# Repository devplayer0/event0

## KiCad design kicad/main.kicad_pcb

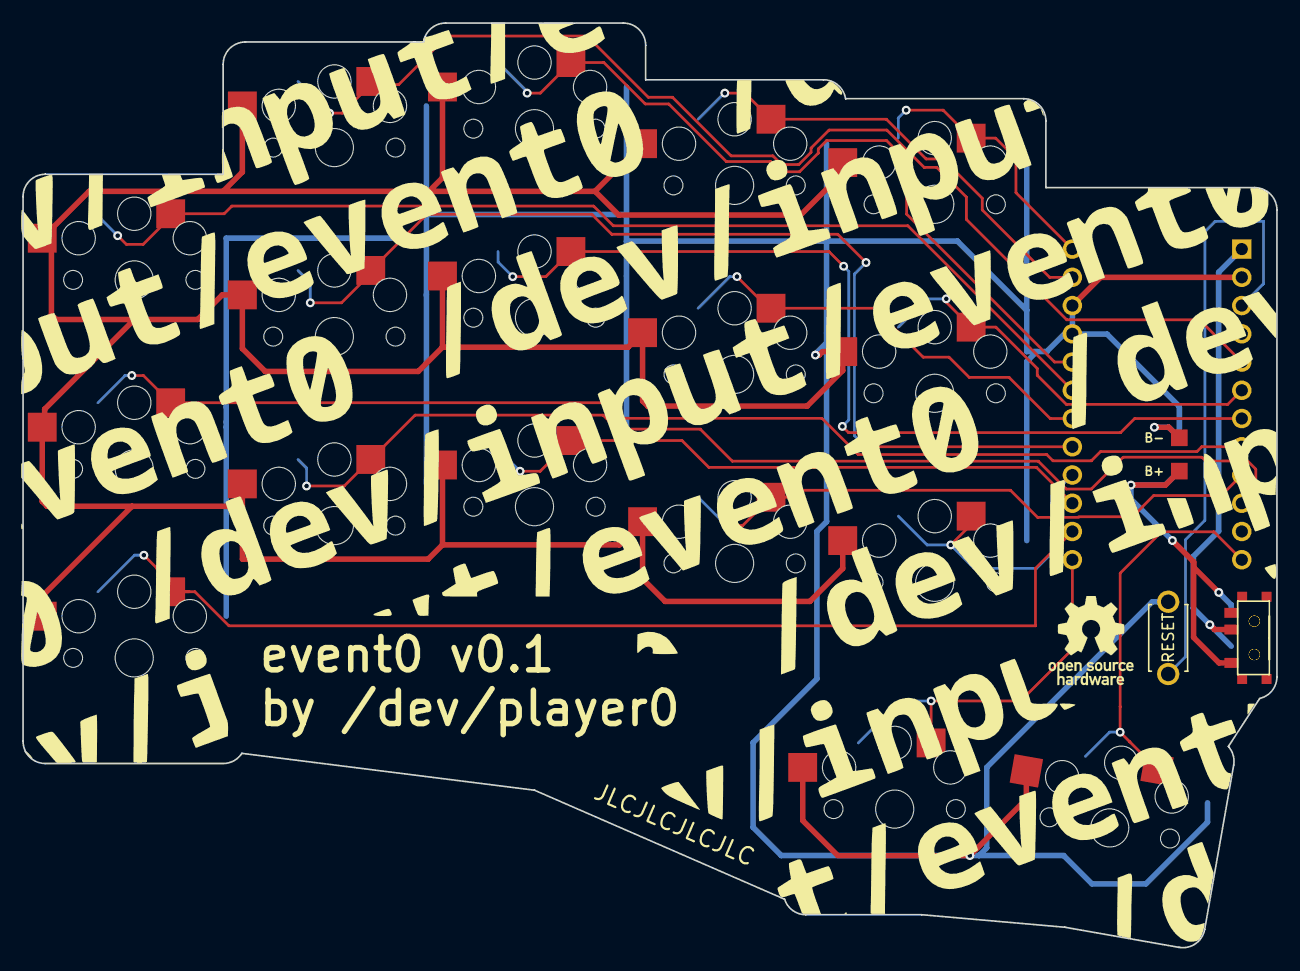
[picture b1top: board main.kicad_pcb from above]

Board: 2 copper layers, 112.8 x 83.2 mm, 23 parts (0 on the bottom side), 21 nets.

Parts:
B1: ResetSW
MCU1: ProMicro
PAD1, PAD2: SMDPad
S1, S2, S3, S4, S5, S6, S7, S8, S9, S10, S11, S12, S13, S14, S15, S16, S17: PG1350
T1, T2: SPDT_C128955

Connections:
Bplus: PAD1.1, T1.1, T2.1
GND: B1.2, MCU1.2, MCU1.15, MCU1.16, PAD2.1, S1.2, S2.2, S3.2, S4.2, S5.2, S6.2, S7.2, S8.2, S9.2, S10.2, S11.2, S12.2, S13.2, S14.2, S15.2, S16.2, S17.2
P0: MCU1.14, S12.1
P1: MCU1.13, S15.1
P2: MCU1.17, S9.1
P3: MCU1.18, S3.1
P4: MCU1.19, S11.1
P5: MCU1.20, S5.1
P6: MCU1.21, S13.1
P7: MCU1.22, S7.1
P8: MCU1.23, S1.1
P9: MCU1.24, S16.1
P10: MCU1.12, S17.1
P14: MCU1.10, S4.1
P15: MCU1.9, S10.1
P18: MCU1.8, S2.1
P19: MCU1.7, S8.1
P20: MCU1.6, S14.1
P21: MCU1.5, S6.1
RAW: MCU1.1, T1.2, T2.2
RST: B1.1, MCU1.3

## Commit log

2022-03-31 Shift controller down a bit
2022-03-31 Add hacky script to generate silkscreen pattern
2022-03-31 Add text to PCB
2022-04-01 Remove battery stuff
2022-04-01 Add silk pattern stuff
2022-04-01 Add KiCad stuff
2022-04-01 Inherit power switch and pads
2022-04-01 Shift JLC order number slightly to match silk mask
2022-04-01 Disable soldered choc footprints
2022-04-01 Create separate right side silkscreen pattern
2022-04-01 Change MCU pinout
2022-04-01 (Maybe) finished PCB
2022-04-16 Add basic flake
2022-04-17 Add ZMK shield
2022-04-24 zmk: Add ESC on right hand of lower layer
